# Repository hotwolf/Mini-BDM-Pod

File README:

This is the website of the Mini-BDM-Pod project.

...see https://hotwolf.github.io/Mini-BDM-Pod/

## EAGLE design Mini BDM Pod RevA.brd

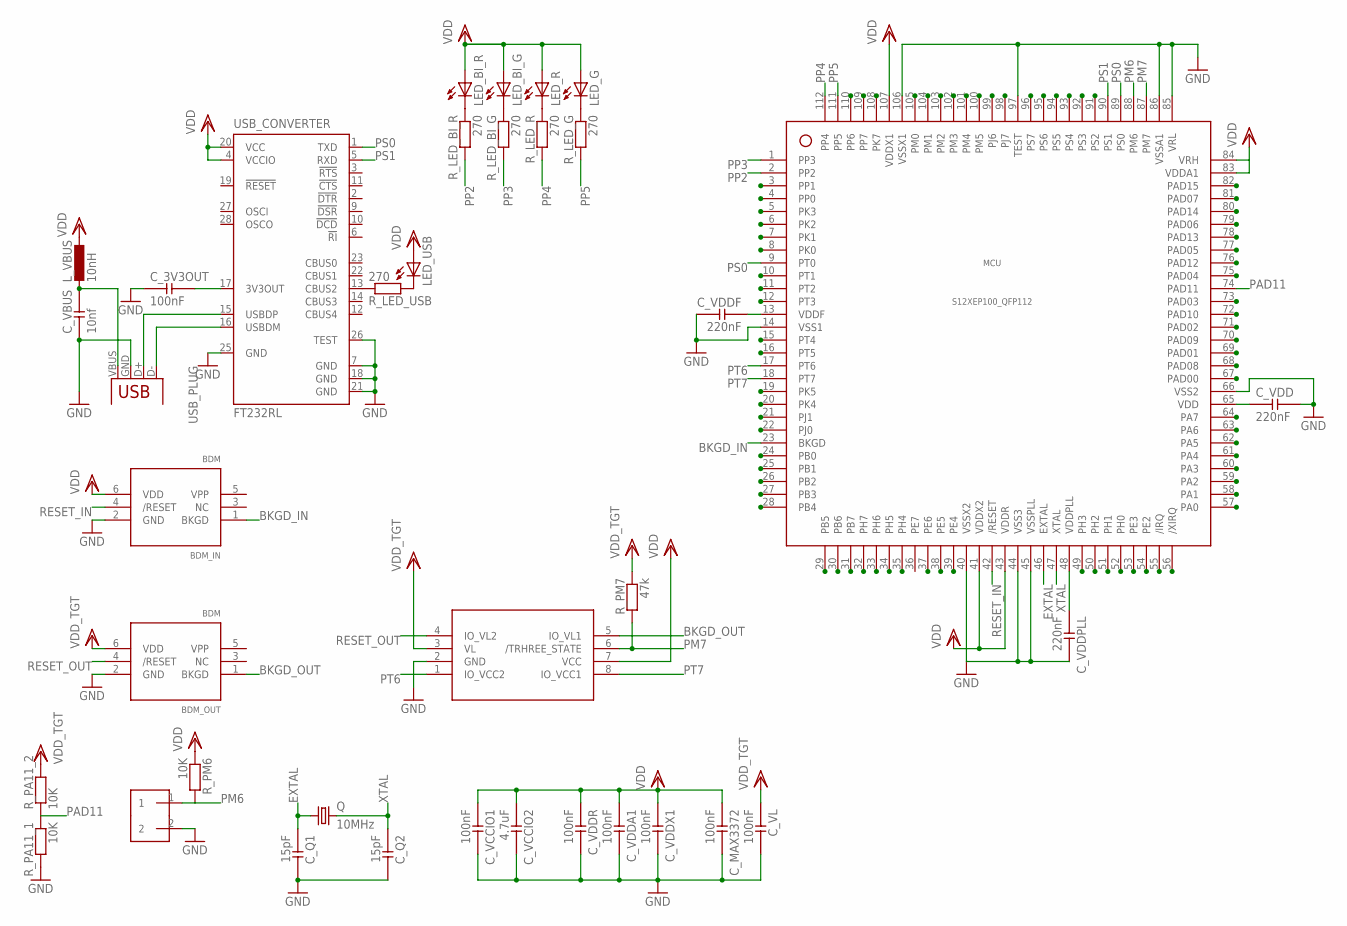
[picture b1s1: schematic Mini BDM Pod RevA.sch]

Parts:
BDM_IN: BDM
BDM_OUT: BDM
C_3V3OUT: 100nF; 0805
C_MAX3372: 100nF; 0805
C_Q1, C_Q2: 15pF; 0805
C_VBUS: 10nf; 0805
C_VCCIO1: 100nF; 0805
C_VCCIO2: 4.7uF; 0805
C_VDD: 220nF; 0805
C_VDDA1: 100nF; 0805
C_VDDF: 220nF; 0805
C_VDDPLL: 220nF; 0805
C_VDDR: 100nF; 0805
C_VDDX1: 100nF; 0805
C_VL: 100nF; 0805
JUMPER: 1X2
LED_BI_G: LED0805; 0805
LED_BI_R: LED0805; 0805
LED_G: LED0805; 0805
LED_R: LED0805; 0805
LED_USB: LED0805; 0805
LEVEL_SHIFTER: MAX3373; SOT-23-MAXIM
L_VBUS: 10nH; 0805
MCU: S12XEP100_QFP112; QFP112
Q: 10MHz; HC49U70
R_LED_BI_G: 270; 0805
R_LED_BI_R: 270; 0805
R_LED_G: 270; 0805
R_LED_R: 270; 0805
R_LED_USB: 270; 0805
R_PA11_1, R_PA11_2: 10K; 0805
R_PM6: 10K; 0805
R_PM7: 47k; 0805
USB_CONVERTER: FT232RL; SSOP28
USB_PLUG: USB_PRINT-A; A

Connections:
3V3OUT: C_3V3OUT.1, USB_CONVERTER.17 (3V3OUT)
BKGD_IN: BDM_IN.1 (BKGD), MCU.23 (BKGD)
BKGD_OUT: BDM_OUT.1 (BKGD), LEVEL_SHIFTER.5 (IO_VL1)
D+: USB_CONVERTER.15 (USBDP), USB_PLUG.D+ (D-)
D-: USB_CONVERTER.16 (USBDM), USB_PLUG.D- (D+)
EXTAL: C_Q1.2, MCU.46 (EXTAL), Q.1
GND: BDM_IN.2 (GND), BDM_OUT.2 (GND), C_3V3OUT.2, C_MAX3372.1, C_Q1.1, C_Q2.1, C_VBUS.2, C_VCCIO1.1, C_VCCIO2.1, C_VDD.1, C_VDDA1.1, C_VDDF.1, C_VDDPLL.1, C_VDDR.1, C_VDDX1.1, C_VL.1, JUMPER.2, LEVEL_SHIFTER.2 (GND), MCU.14 (VSS1), MCU.40 (VSSX2), MCU.44 (VSS3), MCU.45 (VSSPLL), MCU.66 (VSS2), MCU.85 (VRL), MCU.86 (VSSA1), MCU.97 (TEST), MCU.106 (VSSX1), R_PA11_1.1, USB_CONVERTER.7 (GND), USB_CONVERTER.18 (GND), USB_CONVERTER.21 (GND), USB_CONVERTER.25 (GND), USB_CONVERTER.26 (TEST), USB_PLUG.GND (VBUS)
unnamed: R_LED_USB.2, USB_CONVERTER.13 (CBUS2)
unnamed: LED_USB.2 (C), R_LED_USB.1
unnamed: C_VBUS.1, L_VBUS.2, USB_PLUG.VBUS (GND)
unnamed: C_VDD.2, MCU.65 (VDD)
unnamed: LED_BI_R.2 (C), R_LED_BI_R.2
unnamed: LED_BI_G.2 (C), R_LED_BI_G.2
unnamed: LED_R.2 (C), R_LED_R.2
unnamed: LED_G.2 (C), R_LED_G.2
PAD11: MCU.74 (PAD11), R_PA11_1.2, R_PA11_2.2
PM6: JUMPER.1, MCU.88 (PM6), R_PM6.1
PM7: LEVEL_SHIFTER.6 (/TRHREE_STATE), MCU.87 (PM7), R_PM7.1
PP2: MCU.2 (PP2), R_LED_BI_R.1
PP3: MCU.1 (PP3), R_LED_BI_G.1
PP4: MCU.112 (PP4), R_LED_R.1
PP5: MCU.111 (PP5), R_LED_G.1
PS0: MCU.9 (PT0), MCU.89 (PS0), USB_CONVERTER.1 (TXD)
PS1: MCU.90 (PS1), USB_CONVERTER.5 (RXD)
PT6: LEVEL_SHIFTER.1 (IO_VCC2), MCU.17 (PT6)
PT7: LEVEL_SHIFTER.8 (IO_VCC1), MCU.18 (PT7)
RESET_IN: BDM_IN.4 (/RESET), MCU.42 (/RESET)
RESET_OUT: BDM_OUT.4 (/RESET), LEVEL_SHIFTER.4 (IO_VL2)
VDD: BDM_IN.6 (VDD), C_MAX3372.2, C_VCCIO1.2, C_VCCIO2.2, C_VDDA1.2, C_VDDR.2, C_VDDX1.2, LED_BI_G.1 (A), LED_BI_R.1 (A), LED_G.1 (A), LED_R.1 (A), LED_USB.1 (A), LEVEL_SHIFTER.7 (VCC), L_VBUS.1, MCU.41 (VDDX2), MCU.43 (VDDR), MCU.83 (VDDA1), MCU.84 (VRH), MCU.107 (VDDX1), R_PM6.2, USB_CONVERTER.4 (VCCIO), USB_CONVERTER.20 (VCC)
VDDF: C_VDDF.2, MCU.13 (VDDF)
VDDPLL: C_VDDPLL.2, MCU.48 (VDDPLL)
VDD_TGT: BDM_OUT.6 (VDD), C_VL.2, LEVEL_SHIFTER.3 (VL), R_PA11_2.1, R_PM7.2
XTAL: C_Q2.2, MCU.47 (XTAL), Q.2

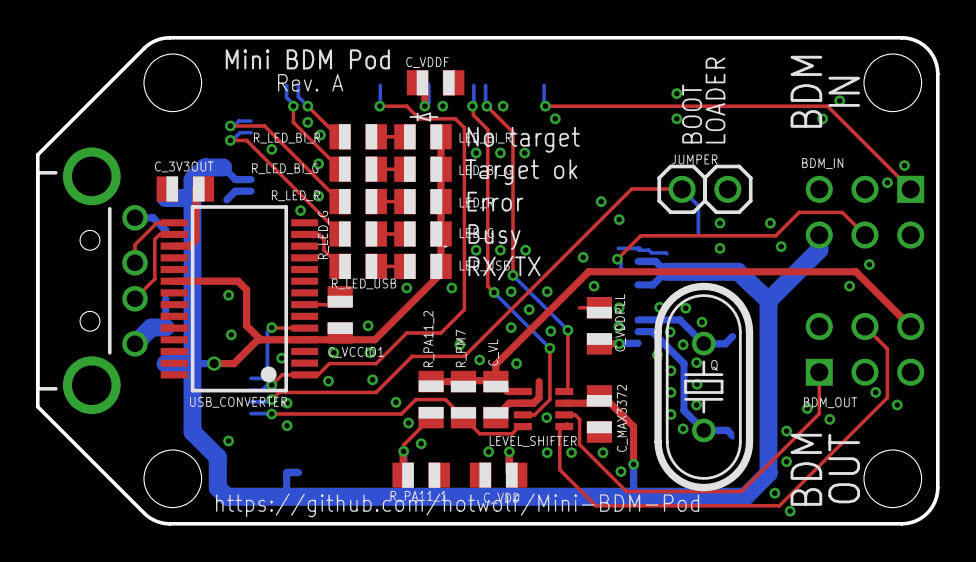
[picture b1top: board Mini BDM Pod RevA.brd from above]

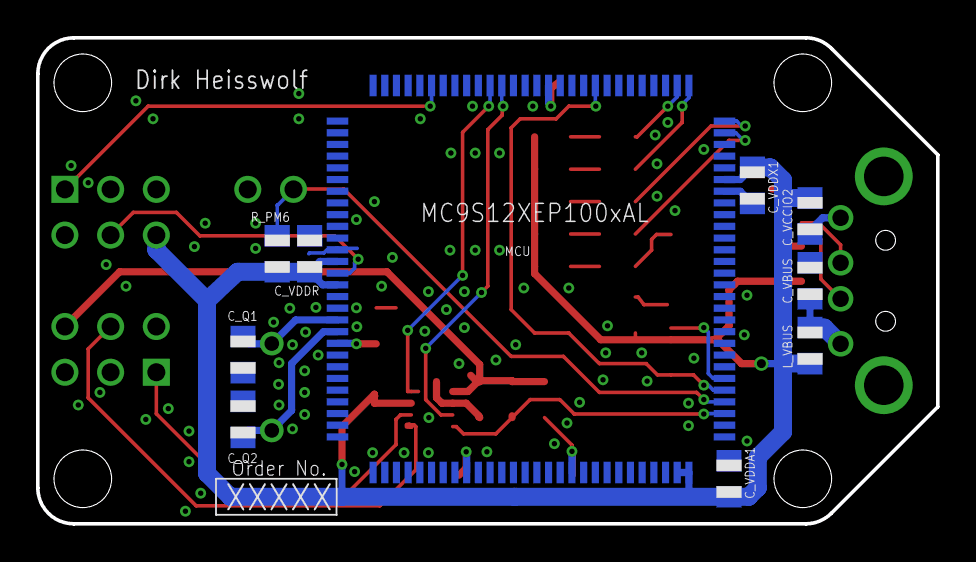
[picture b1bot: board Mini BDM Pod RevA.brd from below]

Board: 2 copper layers, 50.0 x 27.0 mm, 37 parts (10 on the bottom side), 33 nets.

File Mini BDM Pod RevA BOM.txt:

Bill of Materials for the Mini BDM Pod Rev A:
=============================================

ICs:

1x	MC9S12XEP100xAL		LQFP112			MCU
1x	FT232RL			SSOP-28			USB_CONVERTER
1x	MAX3373EEKA+		SOT23			LEVEL_SHIFTER			

Oscillator:
1x	10MHz			Print, pin dist. 7.62mm	Q

Capacitors:

2x	 15pF			0805			C_Q1, C_Q2
1x	 10nF			0805			C_VBUS
5x	100nF			0805			C_3V3OUT, C_MAX3372, C_VCCIO1, C_VDDA1, C_VDDX1, C_VL
4x	220nF			0805			C_VDD, C_VDDF, C_VDDPLL, C_VDDR
1x	4.7uF			0805			C_VCCIO2

Inductors:

1x	10nH			0805			L_VBUS

Resistors:

5x	270			0805			R_LED_BI_G, R_LED_BI_R, R_LED_G, R_LED_R, R_LED_USB
3x	10K			0805			R_PA11_1, R_PA11_2, R_PM6
1x	47K			0805			R_PM7

LEDs:

2x	red			0805			LED_R, LED_BI_R
2x	green			0805			LED_USB, LED_BI_G
1x	yellow			0805			LED_G

Connectors:

1x	USB-A			Print			USB_PLUG
2x	2x3 strait		Print			BDM_IN, BDM_OUT
1x	1x2 bent		Print			JUMPER

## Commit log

2012-03-25 initial release (rev. A)
2012-03-25 added Gerber files
2012-03-26 added BOM
2012-03-26 prepared mounting diagram
2012-03-26 added schematic and mounting plan
2012-03-27 mirrored bottom names for mounting plan
2012-03-28 fixed mounting plan
2012-05-08 added RevB
2012-05-08 added mounting plan and Gerber files
2012-05-29 added Jekyll pages
2012-05-29 fixed wording
2012-06-05 added RevB schematic
2012-06-05 RevB boards have arrived
2012-06-05 fixed link to image
2012-06-06 added post
2012-06-06 fixed project names
2012-06-12 Update master
2012-08-01 RevB pods built
2012-08-02 added up cost of materials
2013-01-08 new post
2013-01-08 fixed post
2013-02-11 minor corrections
2013-02-12 renamed atom feed
2013-02-23 fixed atom feed
2014-09-17 rearranged directories
2014-09-18 fixed file names
2014-12-10 removed order number from layout
2015-01-03 fixed posting
2015-01-03 corrected post
2016-05-13 fixed layout
2016-05-13 converted textile posts to html
2017-02-24 added TicTacToe project
2018-06-08 updated 404 page
2019-05-30 updated related projects
